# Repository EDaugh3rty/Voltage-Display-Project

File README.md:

# Voltage-Display-Project
This project chips were given to us and we had to design a PCB for them and program a CPLD in VHDL.
The goal was to teach VHDL and PCB design. The inputs were different ranges of voltages and depending on which mode it was it would display a different LED output.

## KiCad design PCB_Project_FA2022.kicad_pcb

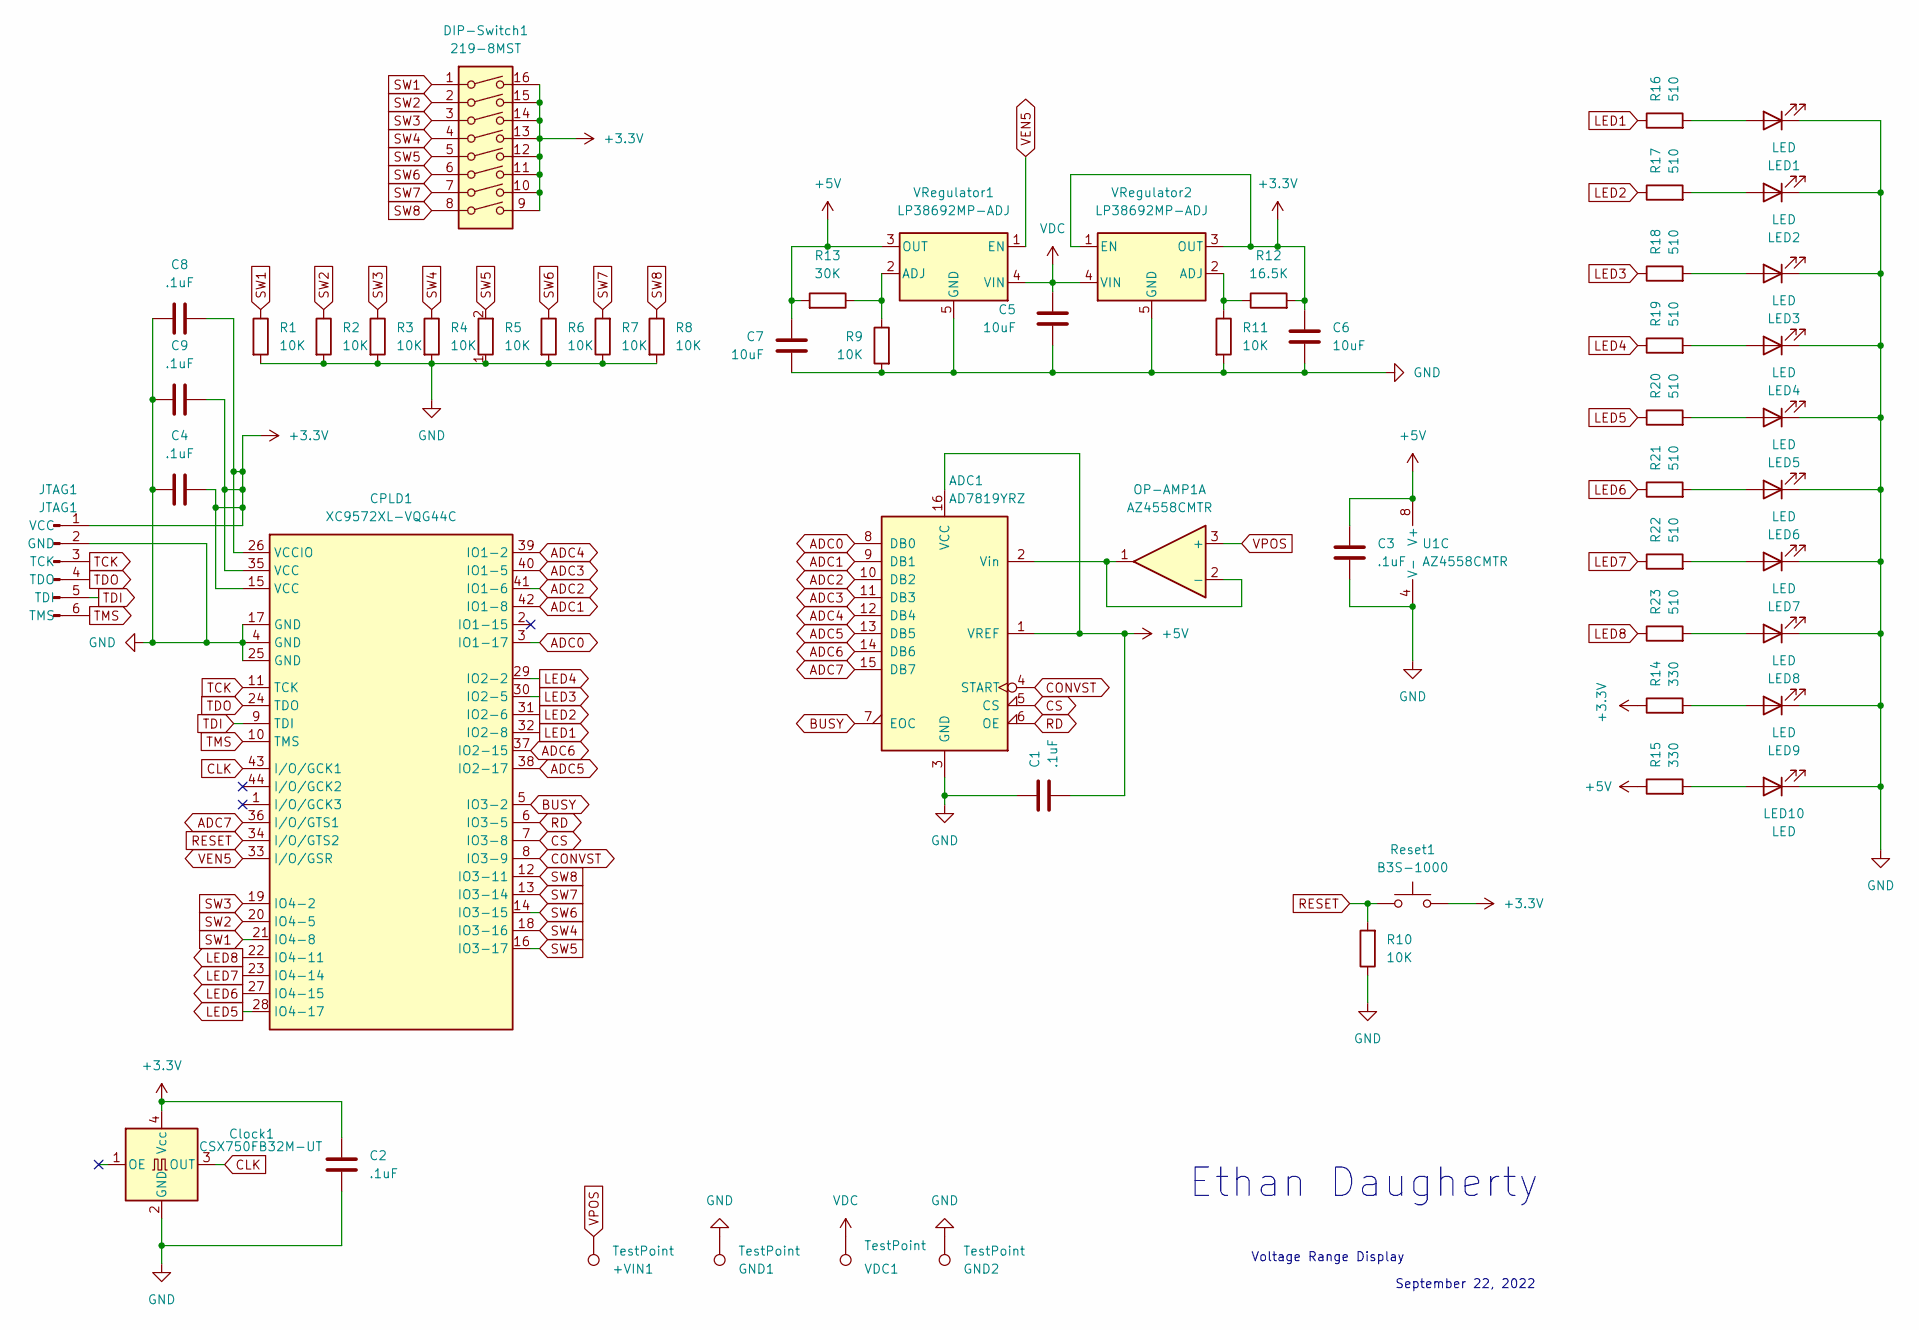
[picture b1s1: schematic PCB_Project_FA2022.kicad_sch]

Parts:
+VIN1: TestPoint; TestPoint_Keystone_5000-5004_Miniature
ADC1: AD7819YRZ; SOIC-16
C1, C2, C3, C4, C8, C9: .1uF; C_0805_2012Metric
C5, C6, C7: 10uF; C_0805_2012Metric
CPLD1: XC9572XL-VQG44C; TQFP-44_10x10mm_P0.8mm
Clock1: CSX750FB32M-UT; Oscillator_SMD_SeikoEpson_SG8002CA-4Pin_7.0x5.0mm
DIP-Switch1: 219-8MST; SW_DIP_SPSTx08_Slide_9.78x22.5mm_W8.61mm_P2.54mm
GND1, GND2: TestPoint; TestPoint_Keystone_5000-5004_Miniature
JTAG1: JTAG1; JTAG
LED1, LED2, LED3, LED4, LED5, LED6, LED7, LED8, LED9, LED10: LED; LED_0805_2012Metric
OP-AMP1: AZ4558CMTR; SOIC-8_3.9x4.9mm_P1.27mm
R1, R2, R3, R4, R5, R6, R7, R8, R9, R10, R11: 10K; R_0805_2012Metric
R12: 16.5K; R_0805_2012Metric
R13: 30K; R_0805_2012Metric
R14, R15: 330; R_0805_2012Metric
R16, R17, R18, R19, R20, R21, R22, R23: 510; R_0805_2012Metric
Reset1: B3S-1000; SW_SPST_B3S-1000
U1: AZ4558CMTR; SOIC-8_3.9x4.9mm_P1.27mm
VDC1: TestPoint; TestPoint_Keystone_5000-5004_Miniature
VRegulator1, VRegulator2: LP38692MP-ADJ; SOT-223-5

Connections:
+3V3: C2.1, C4.1, C6.1, C8.2, C9.1, CPLD1.15 (VCC), CPLD1.26 (VCCIO), CPLD1.35 (VCC), Clock1.4 (Vcc), DIP-Switch1.9, DIP-Switch1.10, DIP-Switch1.11, DIP-Switch1.12, DIP-Switch1.13, DIP-Switch1.14, DIP-Switch1.15, DIP-Switch1.16, JTAG1.1 (VCC), R12.2, R14.1, Reset1.2, VRegulator2.1 (EN), VRegulator2.3 (OUT)
+5V: ADC1.1 (VREF), ADC1.16 (VCC), C1.2, C3.2, C7.1, R13.2, R15.1, U1.8 (V+), VRegulator1.3 (OUT)
ADC0: ADC1.8 (DB0), CPLD1.3 (IO1-17)
ADC1: ADC1.9 (DB1), CPLD1.42 (IO1-8)
ADC2: ADC1.10 (DB2), CPLD1.41 (IO1-6)
ADC3: ADC1.11 (DB3), CPLD1.40 (IO1-5)
ADC4: ADC1.12 (DB4), CPLD1.39 (IO1-2)
ADC5: ADC1.13 (DB5), CPLD1.38 (IO2-17)
ADC6: ADC1.14 (DB6), CPLD1.37 (IO2-15)
ADC7: ADC1.15 (DB7), CPLD1.36 (I/O/GTS1)
BUSY: ADC1.7 (EOC), CPLD1.5 (IO3-2)
CLK: CPLD1.43 (I/O/GCK1), Clock1.3 (OUT)
CONVST: ADC1.4 (START), CPLD1.8 (IO3-9)
CS: ADC1.5 (CS), CPLD1.7 (IO3-8)
GND: ADC1.3 (GND), C1.1, C2.2, C3.1, C4.2, C5.2, C6.2, C7.2, C8.1, C9.2, CPLD1.4 (GND), CPLD1.17 (GND), CPLD1.25 (GND), Clock1.2 (GND), GND1.1, GND2.1, JTAG1.2 (GND), LED1.1 (K), LED2.1 (K), LED3.1 (K), LED4.1 (K), LED5.1 (K), LED6.1 (K), LED7.1 (K), LED8.1 (K), LED9.1 (K), LED10.1 (K), R1.2, R2.2, R3.2, R4.2, R5.1, R6.2, R7.1, R8.2, R9.2, R10.1, R11.2, U1.4 (V-), VRegulator1.5 (GND), VRegulator2.5 (GND)
LED1: CPLD1.32 (IO2-8), R16.1
LED2: CPLD1.31 (IO2-6), R17.1
LED3: CPLD1.30 (IO2-5), R18.1
LED4: CPLD1.29 (IO2-2), R19.1
LED5: CPLD1.28 (IO4-17), R20.1
LED6: CPLD1.27 (IO4-15), R21.1
LED7: CPLD1.23 (IO4-14), R22.1
LED8: CPLD1.22 (IO4-11), R23.1
unnamed: ADC1.2 (Vin), OP-AMP1.1, OP-AMP1.2 (-)
unnamed: LED1.2 (A), R16.2
unnamed: LED2.2 (A), R17.2
unnamed: LED3.2 (A), R18.2
unnamed: LED4.2 (A), R19.2
unnamed: LED5.2 (A), R20.2
unnamed: LED6.2 (A), R21.2
unnamed: LED7.2 (A), R22.2
unnamed: LED8.2 (A), R23.2
unnamed: LED9.2 (A), R14.2
unnamed: LED10.2 (A), R15.2
unnamed: R11.1, R12.1, VRegulator2.2 (ADJ)
unnamed: R9.1, R13.1, VRegulator1.2 (ADJ)
RD: ADC1.6 (OE), CPLD1.6 (IO3-5)
RESET: CPLD1.34 (I/O/GTS2), R10.2, Reset1.1
SW1: CPLD1.21 (IO4-8), DIP-Switch1.1, R1.1
SW2: CPLD1.20 (IO4-5), DIP-Switch1.2, R2.1
SW3: CPLD1.19 (IO4-2), DIP-Switch1.3, R3.1
SW4: CPLD1.18 (IO3-16), DIP-Switch1.4, R4.1
SW5: CPLD1.16 (IO3-17), DIP-Switch1.5, R5.2
SW6: CPLD1.14 (IO3-15), DIP-Switch1.6, R6.1
SW7: CPLD1.13 (IO3-14), DIP-Switch1.7, R7.2
SW8: CPLD1.12 (IO3-11), DIP-Switch1.8, R8.1
TCK: CPLD1.11 (TCK), JTAG1.3 (TCK)
TDI: CPLD1.9 (TDI), JTAG1.5 (TDI)
TDO: CPLD1.24 (TDO), JTAG1.4 (TDO)
TMS: CPLD1.10 (TMS), JTAG1.6 (TMS)
VDC: C5.1, VDC1.1, VRegulator1.4 (VIN), VRegulator2.4 (VIN)
VEN5: CPLD1.33 (I/O/GSR), VRegulator1.1 (EN)
VPOS: +VIN1.1, OP-AMP1.3 (+)

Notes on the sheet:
September 22, 2022
Ethan Daugherty
Voltage Range Display

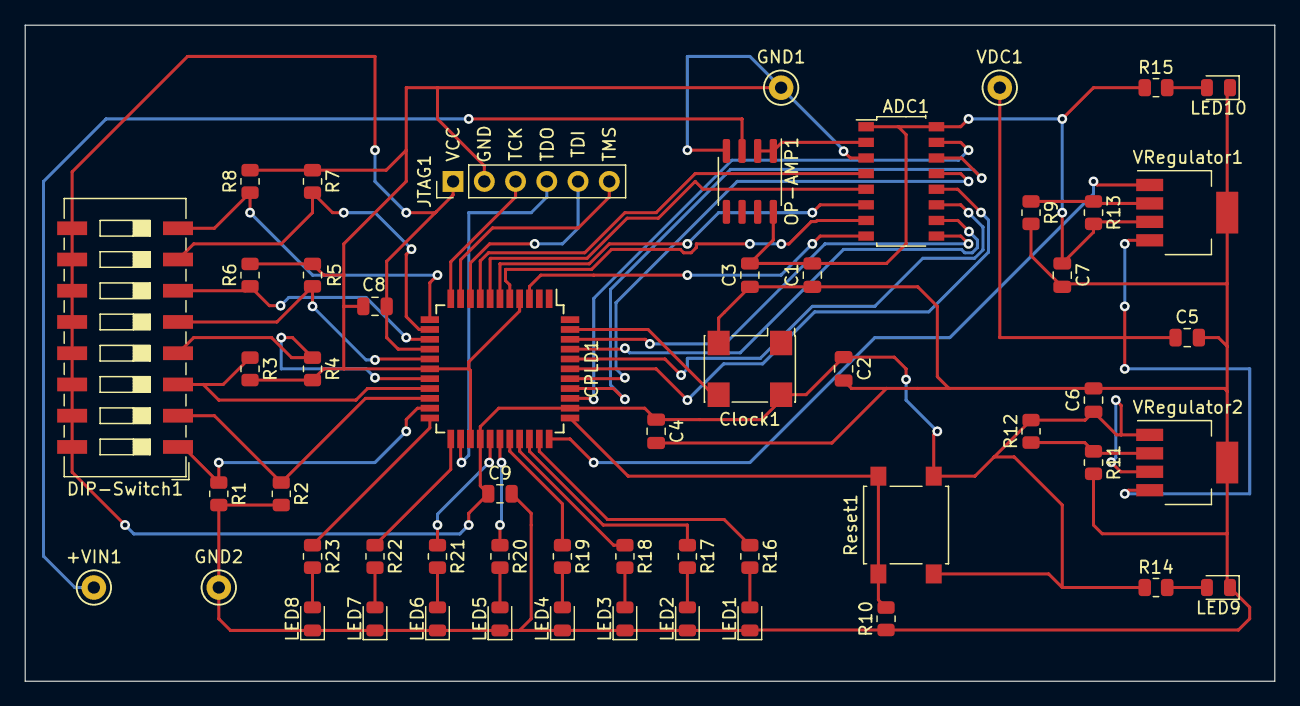
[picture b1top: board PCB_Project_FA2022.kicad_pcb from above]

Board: 2 copper layers, 101.6 x 53.3 mm, 55 parts (0 on the bottom side), 53 nets.
